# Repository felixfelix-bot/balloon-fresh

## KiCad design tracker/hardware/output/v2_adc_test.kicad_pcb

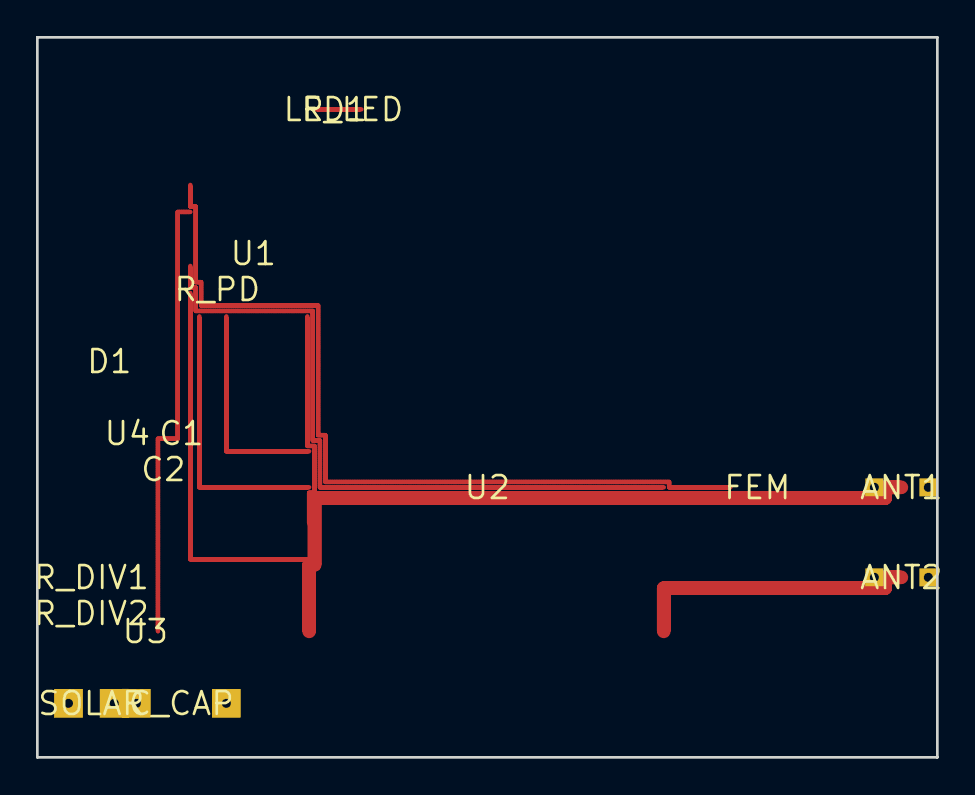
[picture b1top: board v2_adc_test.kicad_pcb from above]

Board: 2 copper layers, 50.0 x 40.0 mm, 17 parts (0 on the bottom side), 18 nets.

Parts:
ANT1: U.FL-868
ANT2: U.FL-2400
C1, C2: 10uF
C_CAP: Supercap
D1: BAT54
FEM: FEM
LED1: LED-0603
R_DIV1, R_DIV2: 100k
R_LED: 330R
R_PD: 10k
SOLAR: Solar-Conn
U1: ESP32-C3
U2: LR2021F33
U3: MAX-M10S
U4: TPS7A02

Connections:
3V3: C2.1, FEM.VCC, R_DIV1.1, U1.VCC, U2.1, U3.1, U4.4
FEM_TX: FEM.TX, U1.GPIO0
GND: ANT1.2, ANT1.3, ANT2.2, ANT2.3, C1.2, C2.2, C_CAP.2, FEM.GND, LED1.K, R_DIV2.2, R_PD.1, SOLAR.2, U1.GND, U1.GND_B, U2.2, U2.8, U2.10, U2.11, U2.16, U2.17, U3.2, U4.2
GPS_RX: U1.GPIO1, U3.3
LED_ANODE: LED1.A, R_LED.2
LR2021_BUSY: U1.GPIO4, U2.7
LR2021_DIO9: U1.GPIO5, U2.13
LR2021_RST: U1.GPIO3, U2.14
RF_2G4_2400: ANT2.1, U2.18
RF_SUB_868: ANT1.1, U2.9
SOLAR_IN: D1.A, SOLAR.1
SPI_MISO: R_PD.2, U1.GPIO2, U2.3
SPI_MOSI: U1.GPIO7, U2.4
SPI_NSS: U1.GPIO10, U2.6
SPI_SCK: U1.GPIO6, U2.5
STATUS_LED: R_LED.1, U1.GPIO9
VCAP: C1.1, C_CAP.1, D1.K, U4.1, U4.3
VDIV_MID: R_DIV1.2, R_DIV2.1, U1.GPIO8

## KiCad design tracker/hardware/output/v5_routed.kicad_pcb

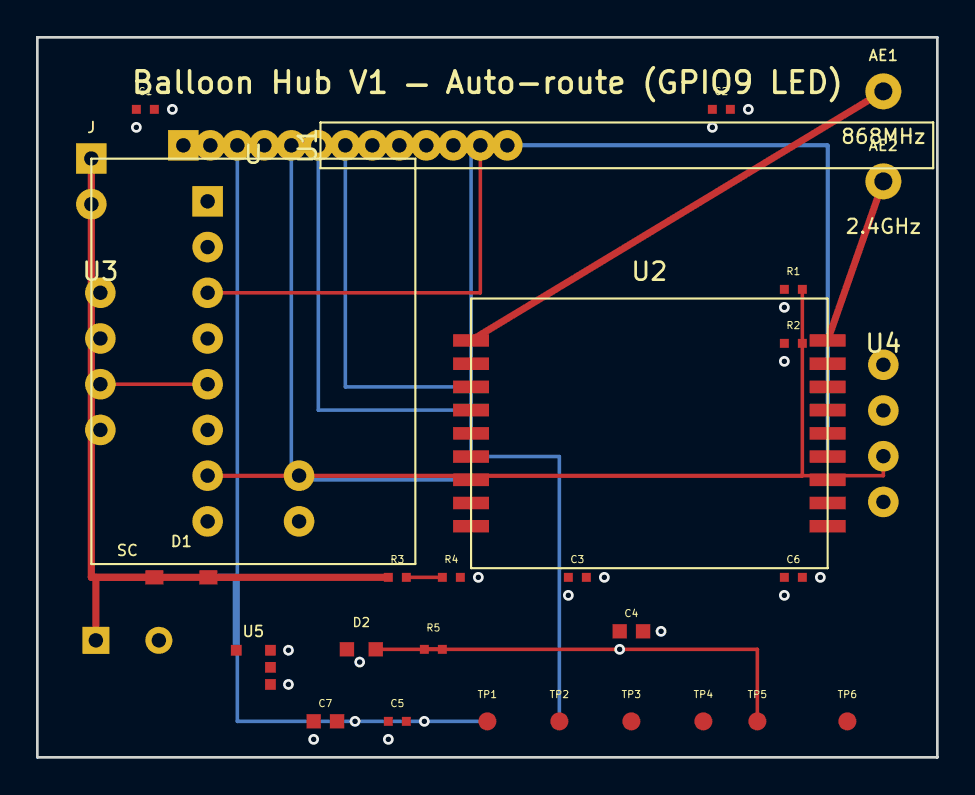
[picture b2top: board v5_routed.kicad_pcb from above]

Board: 4 copper layers, 50.0 x 40.0 mm, 30 parts (0 on the bottom side), 20 nets.

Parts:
AE1: 868MHz; TestPoint_THTPad_D2.0mm_Drill1.0mm
AE2: 2.4GHz; TestPoint_THTPad_D2.0mm_Drill1.0mm
C1, C2, C3, C5, C6: 100nF; C_0402_1005Metric
C4, C7: 10uF; C_0805_2012Metric
D1: BAT54; D_SOD-123
D2: STATUS; LED_0603_1608Metric
J: SOLAR; PinHeader_1x02_P2.54mm_Vertical
R1, R2: 4.7k; R_0402_1005Metric
R3, R4: 1M; R_0402_1005Metric
R5: 330R; R_0402_1005Metric
SC: 1F 5.5V; CP_Radial_D8.0mm_P3.50mm
TP1: SPI0_SCK; TestPoint_Pad_D1.0mm
TP2: SPI0_MOSI; TestPoint_Pad_D1.0mm
TP3: 3V3; TestPoint_Pad_D1.0mm
TP4: GND; TestPoint_Pad_D1.0mm
TP5: LED_GPIO18; TestPoint_Pad_D1.0mm
TP6: FEM_TX_GPIO19; TestPoint_Pad_D1.0mm
U: ESP32-C3-Mini-1; ESP32-C3_Mini_V1_Header
U1: RP2040-Zero; PinHeader_1x13_P2.54mm_Vertical
U2: LoRa2021; LoRa2021_Castellated
U3: MAX-M10S; PinHeader_1x04_P2.54mm_Vertical
U4: MS5611; PinHeader_1x04_P2.54mm_Vertical
U5: TPS7A02; SOT-23-5

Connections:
3V3: C1.1, C2.1, C3.1, C4.1, C5.1, C6.1, C7.1, R1.1, R2.1, TP3.1, U.1, U1.1, U2.1, U3.1, U4.1, U5.5
ESP_TX_RP2040_RX: U.3, U1.12
GND: C1.2, C2.2, C3.2, C4.2, C5.2, C6.2, C7.2, D2.1, J.2, R4.2, SC.2, TP4.1, U.2, U1.2, U1.13, U2.2, U2.8, U2.11, U2.12, U2.18, U3.2, U4.2, U5.2
GPS_TX_ESP_RX: U.5, U3.3
I2C_SDA: R1.2, U.7, U4.3
LED_ANODE: D2.2, R5.2
LR2021_BUSY: U1.7, U2.7
LR2021_DIO9: U1.8, U2.15
LR2021_RST: U1.9, U2.14
RF_2G4_2400: AE2.1, U2.10
RF_SUB_868: AE1.1, U2.9
RP2040_TX_ESP_RX: U.4, U1.11
SOLAR_IN: D1.1, J.1
SPI0_MISO: U1.5, U2.3
SPI0_MOSI: TP2.1, U1.4, U2.4
SPI0_NSS: U1.6, U2.6
SPI0_SCK: TP1.1, U1.3, U2.5
STATUS_LED: R5.1, TP5.1
VCAP: D1.2, R3.1, SC.1, U5.1, U5.3
VDIV_MID: R3.2, R4.1, U.6
